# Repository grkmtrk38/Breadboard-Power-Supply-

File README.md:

# Breadboard Power Supply Module ⚡🔌

A custom-designed, dual-output power supply module built specifically to fit standard MB-102 breadboards. It provides stable 5V and 3.3V power rails, making it an essential tool for prototyping embedded systems and microcontroller projects.

## 📷 Board Preview

## ✨ Features
* **Dual Output Rails:** Provides both **5V** (via LM7805) and **3.3V** (via LM317) regulated outputs simultaneously.
* **Breadboard Compatible:** Pin spacing and layout are perfectly aligned for direct plug-in to standard MB-102 breadboards.
* **Power Input:** Standard barrel jack (J6) for easy connection to wall adapters, plus an onboard power switch (S1).
* **Multiple Connections:** Includes screw terminals and pin headers for versatile power distribution.
* **Visual Indicator:** Onboard LED indicates when the power is active.

## 📂 Repository Structure
* `/Gerber` - Manufacturing files (Gerbers and Drill files) ready for production.
* `breadboard_psu.pdf` - High-resolution schematic file.
* `*.kicad_pro`, `*.kicad_sch`, `*.kicad_pcb` - KiCad 8.0 project workspace files.

## 🛠️ Built With
* **[KiCad](https://www.kicad.org/)** - Open-source PCB design software.

## 🏭 Manufacturing
The fabrication files are located in the `Gerber` directory. You can directly compress this folder into a `.zip` file and upload it to your preferred PCB manufacturer (such as JLCPCB or PCBWay). 

**Board Specifications:**
* **Layers:** 2
* **Components:** Through-hole (THT) for easy hand-soldering.
* **Regulators:** LM7805 (TO-220) and LM317 (TO-220).

## 📄 License
This project is open-source and available under the [MIT License](LICENSE).

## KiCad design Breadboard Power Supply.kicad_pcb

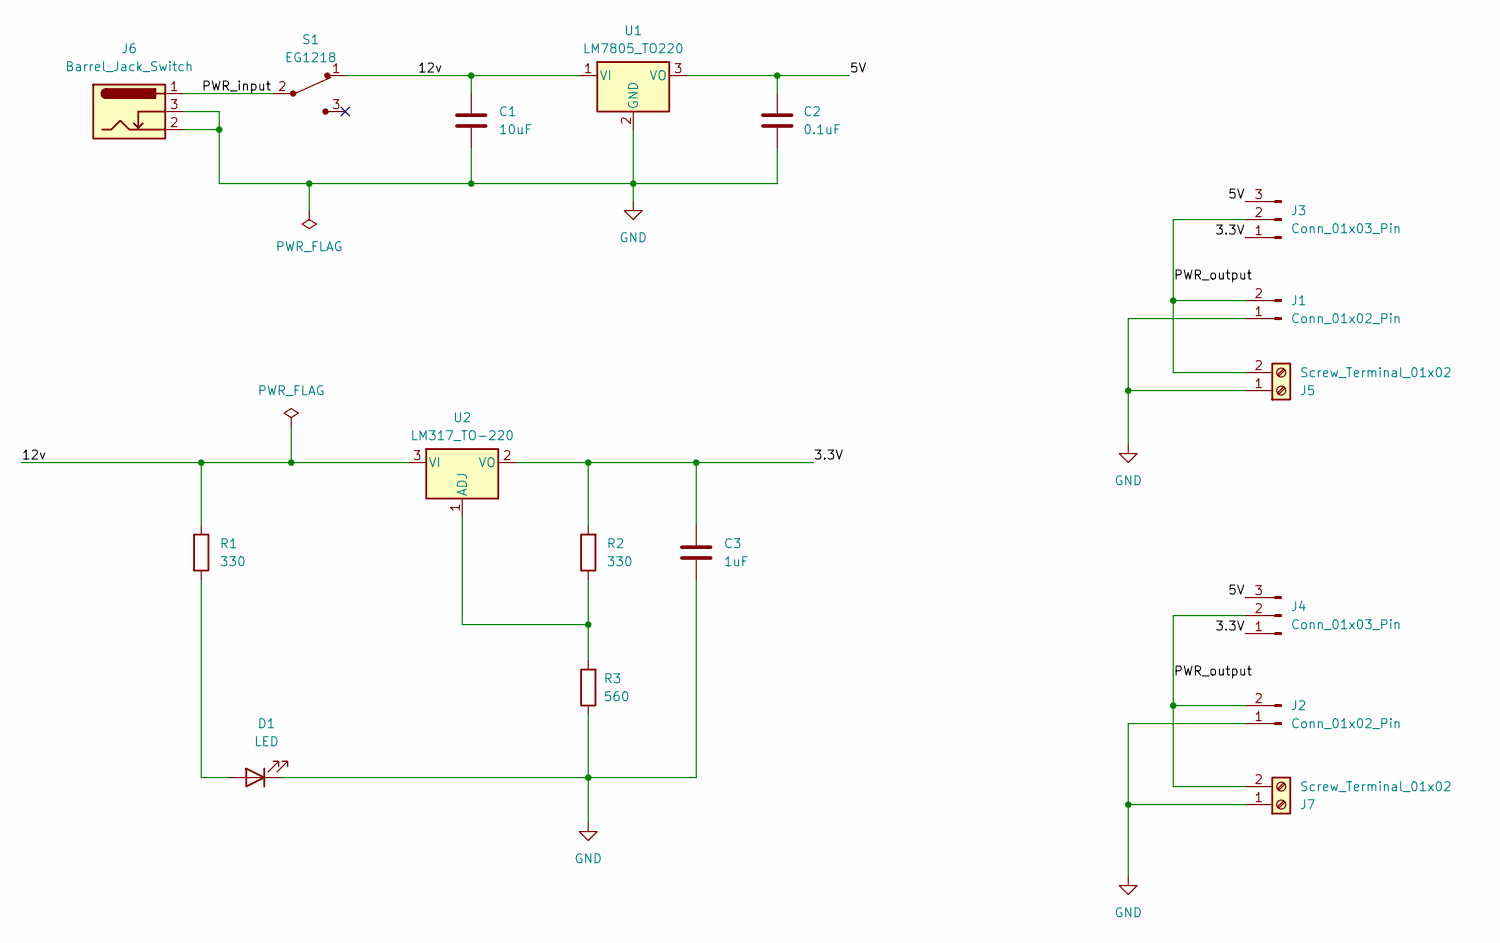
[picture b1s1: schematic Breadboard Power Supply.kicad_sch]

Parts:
C1: 10uF; C_Disc_D3.0mm_W1.6mm_P2.50mm
C2: 0.1uF; C_Disc_D3.0mm_W1.6mm_P2.50mm
C3: 1uF; C_Disc_D3.0mm_W1.6mm_P2.50mm
D1: LED; LED_D5.0mm
J1, J2: Conn_01x02_Pin; PinHeader_1x02_P2.54mm_Vertical
J3, J4: Conn_01x03_Pin; PinHeader_1x03_P2.54mm_Vertical
J5, J7: Screw_Terminal_01x02; TerminalBlock_Phoenix_MKDS-1,5-2-5.08_1x02_P5.08mm_Horizont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
J6: Barrel_Jack_Switch; BarrelJack_Horizontal
R1, R2: 330; R_Axial_DIN0204_L3.6mm_D1.6mm_P7.62mm_Horizontal
R3: 560; R_Axial_DIN0204_L3.6mm_D1.6mm_P7.62mm_Horizontal
S1: EG1218; Switch_Slide_11.6x4mm_EG1218; MPN EG1218; Digi-Key_PN EG1903-ND
U1: LM7805_TO220; TO-220-3_Vertical
U2: LM317_TO-220; TO-220-3_Vertical

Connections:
/3.3V: C3.1, J3.1, J4.1, R2.2, U2.2 (VO)
/5V: C2.1, J3.3, J4.3, U1.3 (VO)
/12v: C1.1, R1.1, S1.1, U1.1 (VI), U2.3 (VI)
/PWR_input: J6.1, S1.2
/PWR_output: J1.2, J2.2, J3.2, J4.2, J5.2, J7.2
GND: C1.2, C2.2, C3.2, D1.1 (K), J1.1, J2.1, J5.1, J6.2, J6.3, J7.1, R3.1, U1.2 (GND)
unnamed: D1.2 (A), R1.2
unnamed: R2.1, R3.2, U2.1 (ADJ)

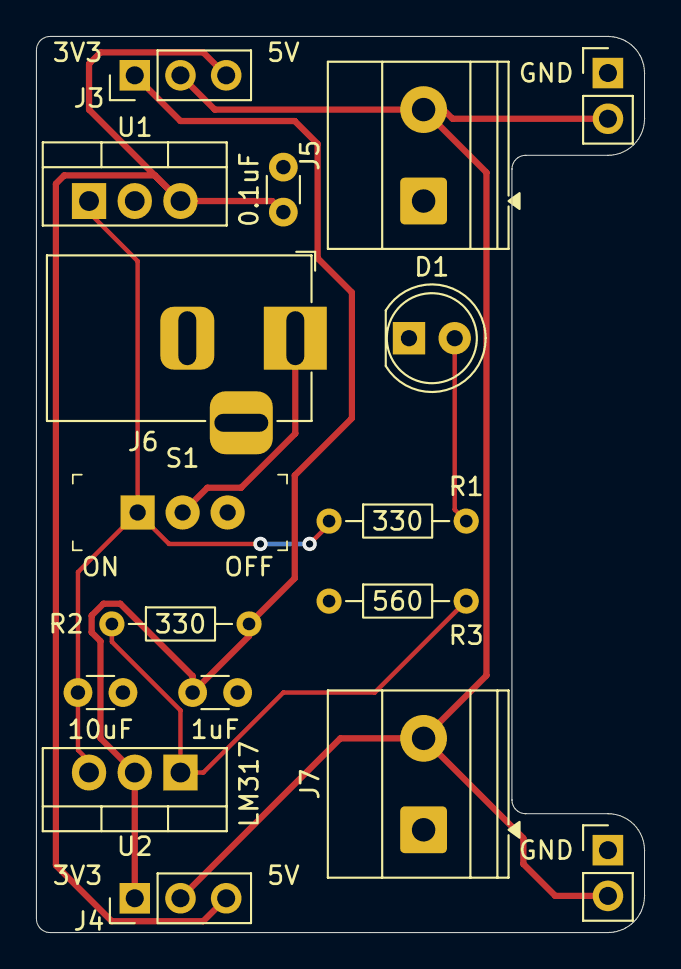
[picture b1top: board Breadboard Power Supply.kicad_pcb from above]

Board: 2 copper layers, 33.8 x 49.8 mm, 17 parts (0 on the bottom side), 8 nets.
